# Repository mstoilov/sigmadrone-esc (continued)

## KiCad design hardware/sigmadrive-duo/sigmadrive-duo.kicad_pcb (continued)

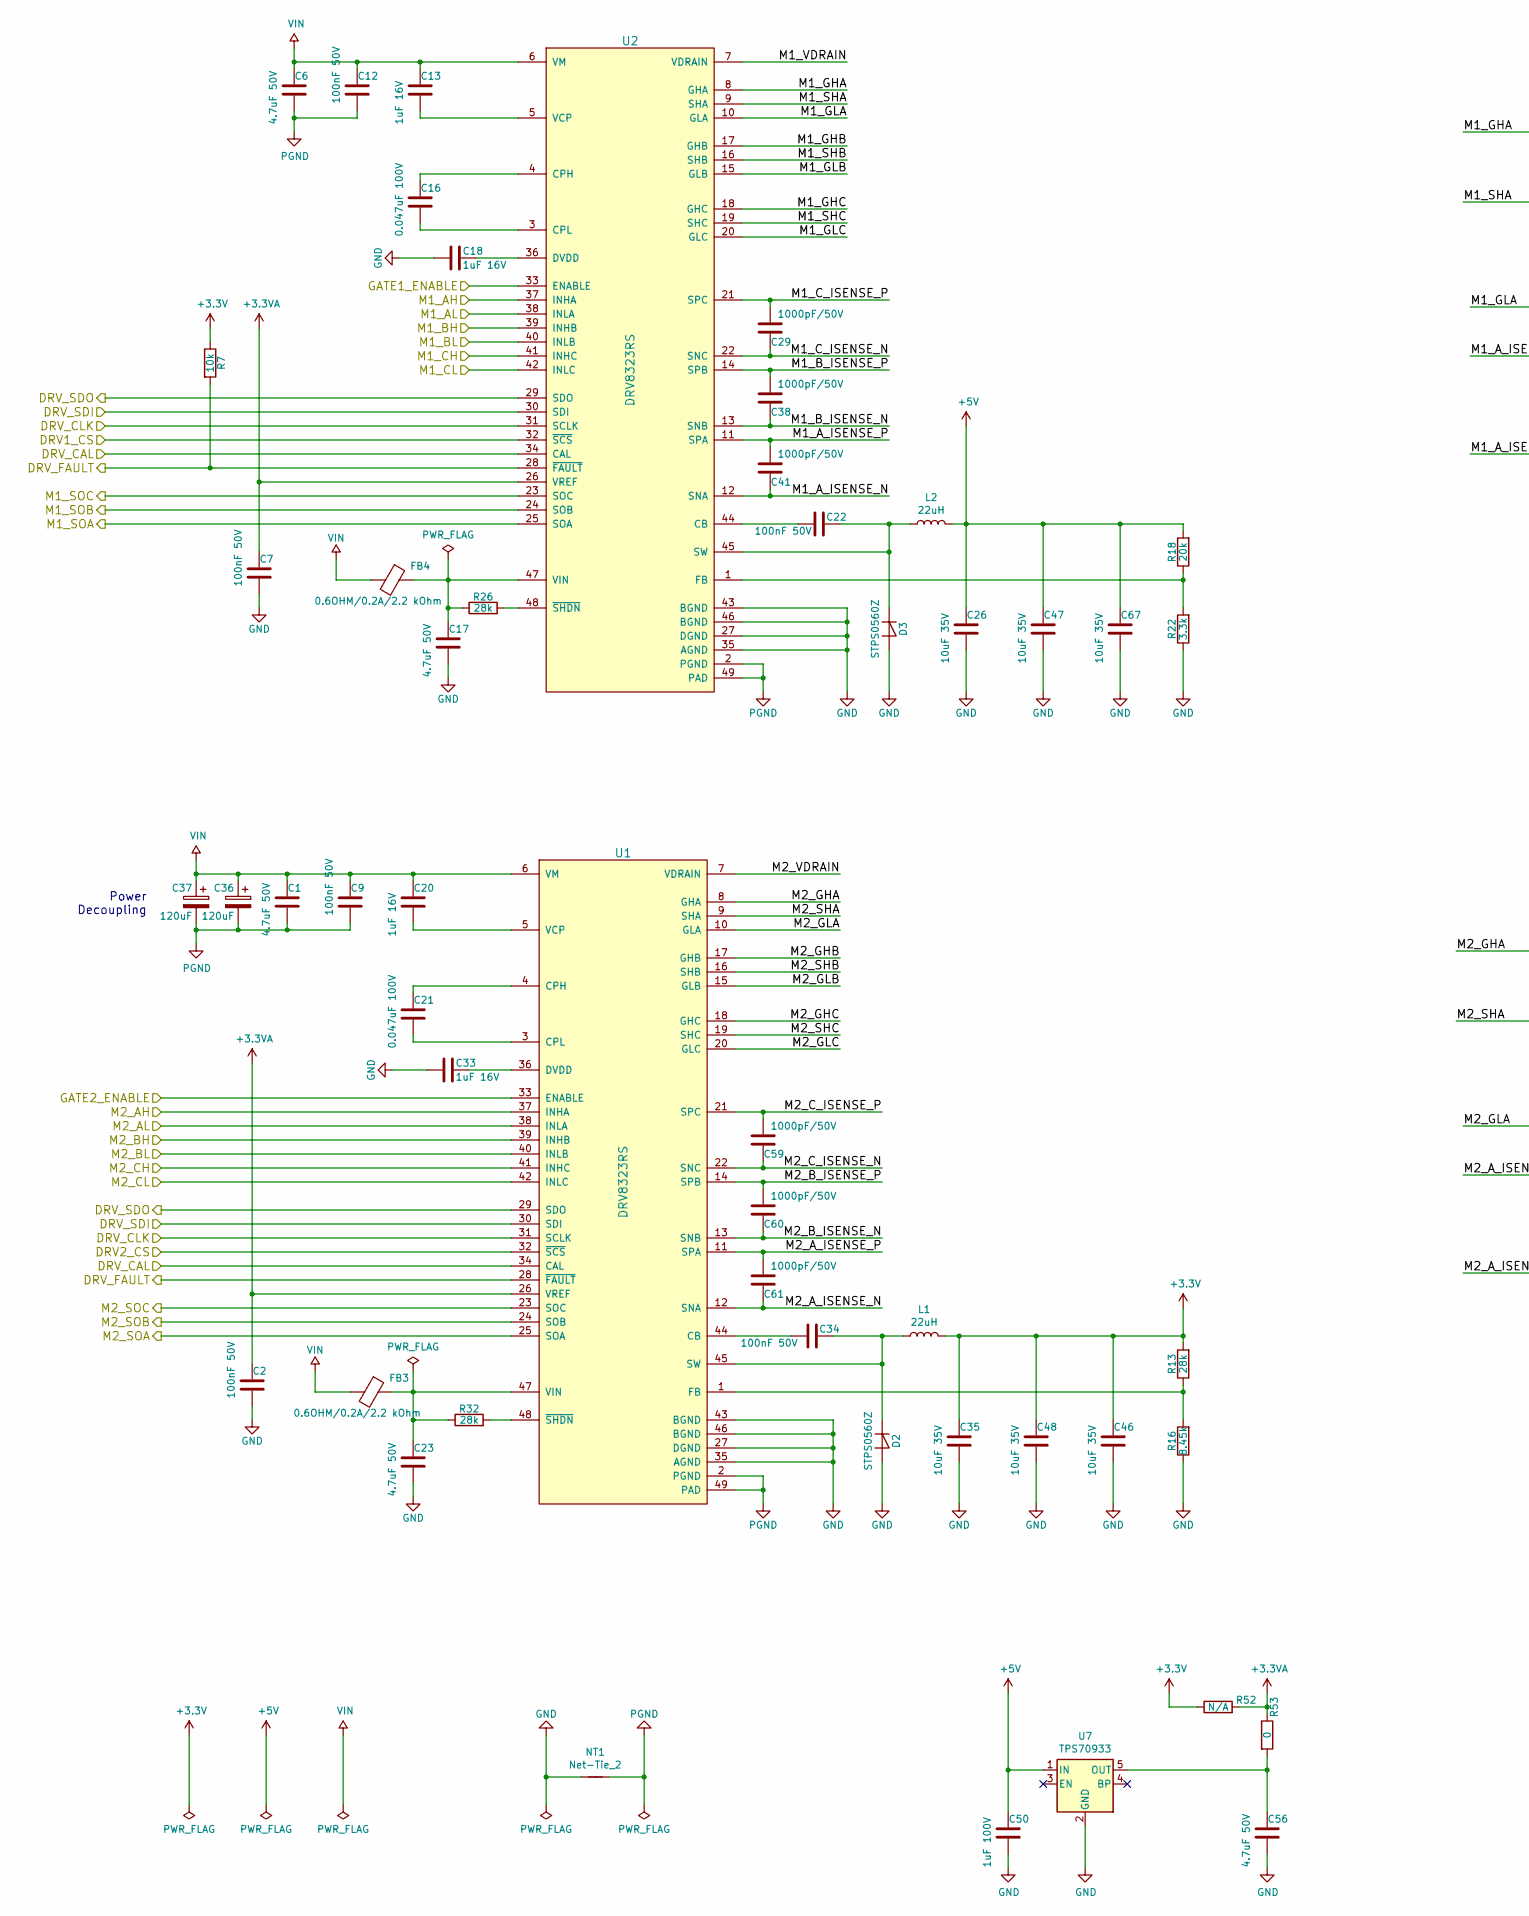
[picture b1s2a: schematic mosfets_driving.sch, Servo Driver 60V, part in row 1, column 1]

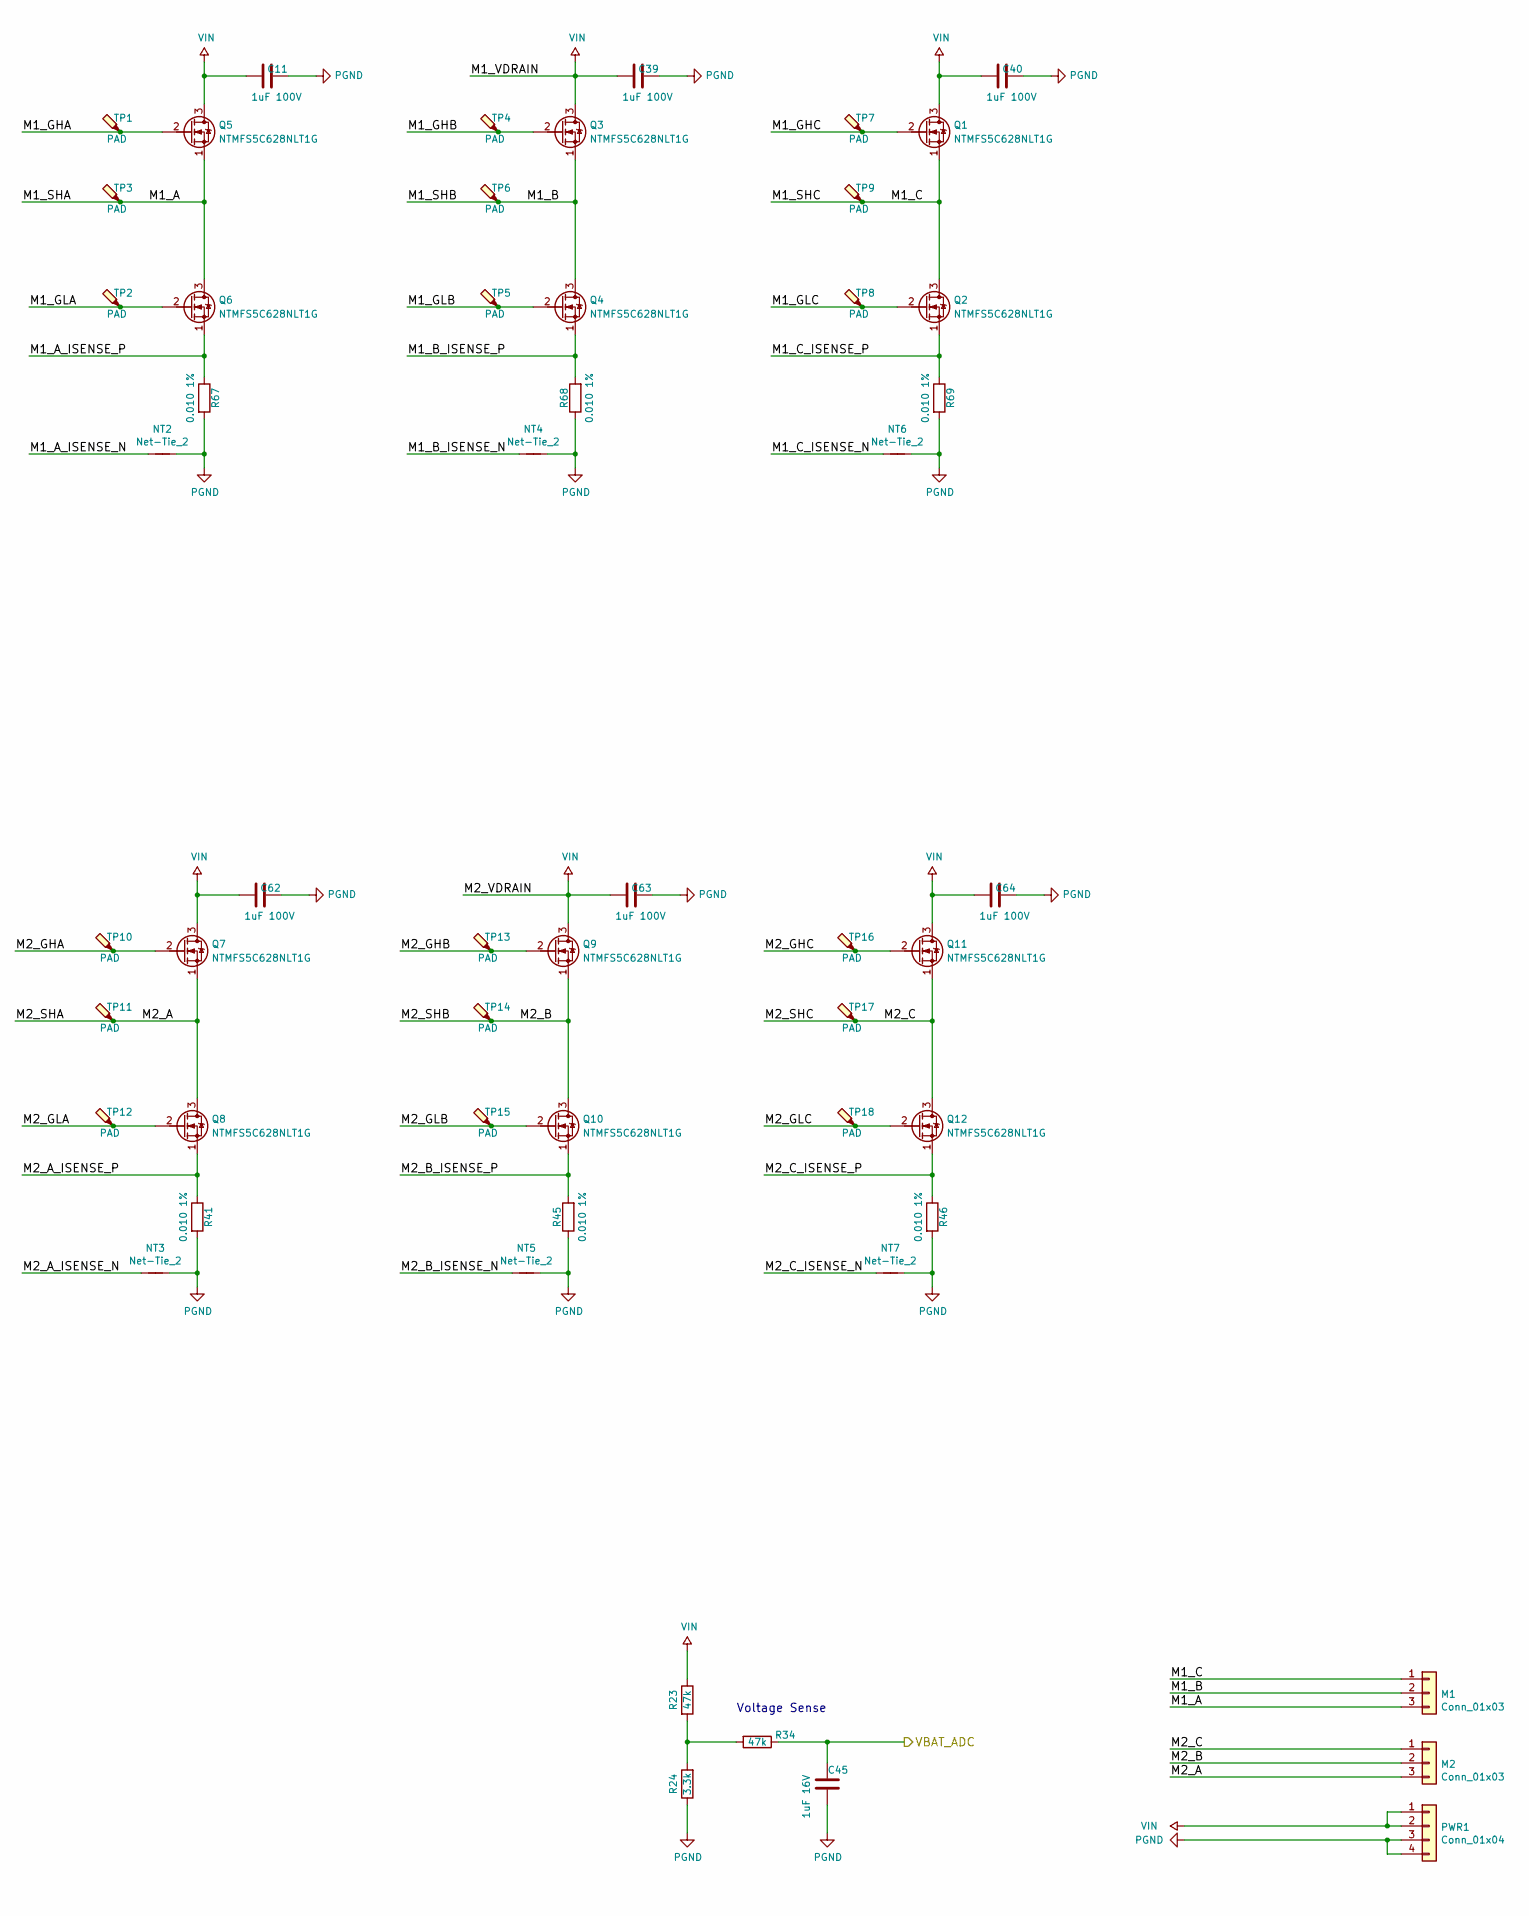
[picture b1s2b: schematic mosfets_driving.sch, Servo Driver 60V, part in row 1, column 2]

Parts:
C1, C6, C17, C23, C56: 4.7uF 50V; C_0805_2012Metric; Part 490-10751-2-ND
C2, C7, C9, C12, C22, C34: 100nF 50V; C_0603_1608Metric; Part 490-4779-2-ND
C11, C39, C40, C50, C62, C63, C64: 1uF 100V; C_0805_2012Metric; Part 445-6804-2-ND
C13, C18, C20, C33, C45: 1uF 16V; C_0603_1608Metric; Part 732-7971-1-ND
C16, C21: 0.047uF 100V; C_0805_2012Metric; Part 490-4969-1-ND
C26, C35, C46, C47, C48, C67: 10uF 35V; C_0805_2012Metric; Part 445-14419-6-ND
C29, C38, C41, C59, C60, C61: 1000pF/50V; C_0603_1608Metric; Part 1276-1091-2-ND
C36, C37: 120uF; CP_Elec_10x10; Part P19316CT-ND
D2, D3: STPS0560Z; D_SOD-123; Part 497-3787-1-ND
FB3, FB4: 0.6OHM/0.2A/2.2 kOhm; R_0603_1608Metric; Part 732-1609-1-ND
L1, L2: 22uH; L_Wuerth_WE-TPC-4828; Part 732-1107-1-ND
M1, M2: Conn_01x03; Molex_Micro-Fit_3.0_43650-0300_1x03_P3.00mm_Horizontal
NT1, NT2, NT3, NT4, NT5, NT6, NT7: Net-Tie_2; NetTie-2_SMD_Pad0.5mm
PWR1: Conn_01x04; Molex_Micro-Fit_3.0_43650-0400_1x04_P3.00mm_Horizontal
Q1, Q2, Q3, Q4, Q5, Q6, Q7, Q8, Q9, Q10, Q11, Q12: NTMFS5C628NLT1G; PQFN_5x6_SGD; Part NTMFS5C628NLT1GOSDKR-ND
R7: 10k; R_0603_1608Metric; Part 311-10.0KHRCT-ND
R13, R26, R32: 28k; R_0603_1608Metric; Part 311-28.0KHRCT-ND
R16: 8.45k; R_0603_1608Metric; Part 311-8.45KHRCT-ND
R18: 20k; R_0603_1608Metric; Part 311-20.0KHRTR-ND
R22, R24: 3.3k; R_0603_1608Metric; Part 311-3.30KHRCT-ND
R23, R34: 47k; R_0603_1608Metric; Part 311-47KDCT-ND
R41, R45, R46, R67, R68, R69: 0.010 1%; R_2512_6332Metric; Part CRA2512-FZ-R010ELFCT-ND
R52: N/A; R_0603_1608Metric; Part 311-0.0GRTR-ND
R53: 0; R_0603_1608Metric; Part 311-0.0GRTR-ND
TP1, TP2, TP3, TP4, TP5, TP6, TP7, TP8, TP9, TP10, TP11, TP12, TP13, TP14, TP15, TP16, TP17, TP18: PAD; TestPoint_Pad_D1.0mm
U1, U2: DRV8323RS; QFN-48-1EP_7x7mm_P0.5mm_EP5.45x5.45mm_ThermalVias; Part 296-47769-1-ND
U7: TPS70933; SOT-23-5; Part 296-35483-1-ND

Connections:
+3.3VA: C2.1, C7.1, R52.2, R53.1, U1.26 (VREF), U2.26 (VREF); also elsewhere on the board
+5V: C26.1, C47.1, C50.1, C67.1, L2.2, R18.2, U7.1 (IN); also elsewhere on the board
/MCU/DRV1_CS: U2.32 (~SCS); also elsewhere on the board
/MCU/DRV2_CS: U1.32 (~SCS); also elsewhere on the board
/MCU/DRV_CAL: U1.34 (CAL), U2.34 (CAL); also elsewhere on the board
/MCU/DRV_CLK: U1.31 (SCLK), U2.31 (SCLK); also elsewhere on the board
/MCU/DRV_FAULT: R7.2, U1.28 (~FAULT), U2.28 (~FAULT); also elsewhere on the board
/MCU/DRV_SDI: U1.30 (SDI), U2.30 (SDI); also elsewhere on the board
/MCU/DRV_SDO: U1.29 (SDO), U2.29 (SDO); also elsewhere on the board
/MCU/GATE1_ENABLE: U2.33 (ENABLE); also elsewhere on the board
/MCU/GATE2_ENABLE: U1.33 (ENABLE); also elsewhere on the board
/MCU/M1_AH: U2.37 (INHA); also elsewhere on the board
/MCU/M1_AL: U2.38 (INLA); also elsewhere on the board
/MCU/M1_BH: U2.39 (INHB); also elsewhere on the board
/MCU/M1_BL: U2.40 (INLB); also elsewhere on the board
/MCU/M1_CH: U2.41 (INHC); also elsewhere on the board
/MCU/M1_CL: U2.42 (INLC); also elsewhere on the board
/MCU/M1_IA_FB: U2.25 (SOA); also elsewhere on the board
/MCU/M1_IB_FB: U2.24 (SOB); also elsewhere on the board
/MCU/M1_IC_FB: U2.23 (SOC); also elsewhere on the board
/MCU/M2_AH: U1.37 (INHA); also elsewhere on the board
/MCU/M2_AL: U1.38 (INLA); also elsewhere on the board
/MCU/M2_BH: U1.39 (INHB); also elsewhere on the board
/MCU/M2_BL: U1.40 (INLB); also elsewhere on the board
/MCU/M2_CH: U1.41 (INHC); also elsewhere on the board
/MCU/M2_CL: U1.42 (INLC); also elsewhere on the board
/MCU/M2_IA_FB: U1.25 (SOA); also elsewhere on the board
/MCU/M2_IB_FB: U1.24 (SOB); also elsewhere on the board
/MCU/M2_IC_FB: U1.23 (SOC); also elsewhere on the board
/MCU/VBAT_ADC: C45.1, R34.1; also elsewhere on the board
/MOSFETs/M1_A: M1.3, Q5.1 (S), Q6.3 (D), TP3.1, U2.9 (SHA)
/MOSFETs/M1_A_ISENSE_N: C41.1, NT2.1, U2.12 (SNA)
/MOSFETs/M1_A_ISENSE_P: C41.2, Q6.1 (S), R67.1, U2.11 (SPA)
/MOSFETs/M1_B: M1.2, Q3.1 (S), Q4.3 (D), TP6.1, U2.16 (SHB)
/MOSFETs/M1_B_ISENSE_N: C38.1, NT4.1, U2.13 (SNB)
/MOSFETs/M1_B_ISENSE_P: C38.2, Q4.1 (S), R68.2, U2.14 (SPB)
/MOSFETs/M1_C: M1.1, Q1.1 (S), Q2.3 (D), TP9.1, U2.19 (SHC)
/MOSFETs/M1_C_ISENSE_N: C29.1, NT6.1, U2.22 (SNC)
/MOSFETs/M1_C_ISENSE_P: C29.2, Q2.1 (S), R69.1, U2.21 (SPC)
/MOSFETs/M1_GHA: Q5.2 (G), TP1.1, U2.8 (GHA)
/MOSFETs/M1_GHB: Q3.2 (G), TP4.1, U2.17 (GHB)
/MOSFETs/M1_GHC: Q1.2 (G), TP7.1, U2.18 (GHC)
/MOSFETs/M1_GLA: Q6.2 (G), TP2.1, U2.10 (GLA)
/MOSFETs/M1_GLB: Q4.2 (G), TP5.1, U2.15 (GLB)
/MOSFETs/M1_GLC: Q2.2 (G), TP8.1, U2.20 (GLC)
/MOSFETs/M2_A: M2.3, Q7.1 (S), Q8.3 (D), TP11.1, U1.9 (SHA)
/MOSFETs/M2_A_ISENSE_N: C61.1, NT3.1, U1.12 (SNA)
/MOSFETs/M2_A_ISENSE_P: C61.2, Q8.1 (S), R41.1, U1.11 (SPA)
/MOSFETs/M2_B: M2.2, Q9.1 (S), Q10.3 (D), TP14.1, U1.16 (SHB)
/MOSFETs/M2_B_ISENSE_N: C60.1, NT5.1, U1.13 (SNB)
/MOSFETs/M2_B_ISENSE_P: C60.2, Q10.1 (S), R45.2, U1.14 (SPB)
/MOSFETs/M2_C: M2.1, Q11.1 (S), Q12.3 (D), TP17.1, U1.19 (SHC)
/MOSFETs/M2_C_ISENSE_N: C59.1, NT7.1, U1.22 (SNC)
/MOSFETs/M2_C_ISENSE_P: C59.2, Q12.1 (S), R46.1, U1.21 (SPC)
/MOSFETs/M2_GHA: Q7.2 (G), TP10.1, U1.8 (GHA)
/MOSFETs/M2_GHB: Q9.2 (G), TP13.1, U1.17 (GHB)
/MOSFETs/M2_GHC: Q11.2 (G), TP16.1, U1.18 (GHC)
/MOSFETs/M2_GLA: Q8.2 (G), TP12.1, U1.10 (GLA)
/MOSFETs/M2_GLB: Q10.2 (G), TP15.1, U1.15 (GLB)
/MOSFETs/M2_GLC: Q12.2 (G), TP18.1, U1.20 (GLC)
GND: C2.2, C7.2, C17.2, C18.2, C23.2, C26.2, C33.2, C35.2, C46.2, C47.2, C48.2, C50.2, C56.2, C67.2, D2.2 (A), D3.2 (A), NT1.1, R16.1, R22.1, U1.27 (DGND), U1.35 (AGND), U1.43 (BGND), U1.46 (BGND), U2.27 (DGND), U2.35 (AGND), U2.43 (BGND), U2.46 (BGND), U7.2 (GND); also elsewhere on the board
unnamed: C13.2, U2.5 (VCP)
unnamed: C16.1, U2.4 (CPH)
unnamed: C16.2, U2.3 (CPL)
unnamed: C17.1, FB4.1, R26.1, U2.47 (VIN)
unnamed: C18.1, U2.36 (DVDD)
unnamed: C20.2, U1.5 (VCP)
unnamed: C21.1, U1.4 (CPH)
unnamed: C21.2, U1.3 (CPL)
unnamed: C22.1, U2.44 (CB)
unnamed: C22.2, D3.1 (K), L2.1, U2.45 (SW)
unnamed: C23.1, FB3.1, R32.1, U1.47 (VIN)
unnamed: C33.1, U1.36 (DVDD)
unnamed: C34.1, U1.44 (CB)
unnamed: C34.2, D2.1 (K), L1.1, U1.45 (SW)
unnamed: C56.1, R53.2, U7.5 (OUT)
unnamed: R13.1, R16.2, U1.1 (FB)
unnamed: R18.1, R22.2, U2.1 (FB)
unnamed: R23.2, R24.2, R34.2
unnamed: R26.2, U2.48 (~SHDN)
unnamed: R32.2, U1.48 (~SHDN)
PGND: C1.2, C6.2, C9.2, C11.2, C12.2, C36.2, C37.2, C39.2, C40.2, C45.2, C62.2, C63.2, C64.2, NT1.2, NT2.2, NT3.2, NT4.2, NT5.2, NT6.2, NT7.2, PWR1.3, PWR1.4, R24.1, R41.2, R45.1, R46.2, R67.2, R68.1, R69.2, U1.2 (PGND), U1.49 (PAD), U2.2 (PGND), U2.49 (PAD)
VIN: C1.1, C6.1, C9.1, C11.1, C12.1, C13.1, C20.1, C36.1, C37.1, C39.1, C40.1, C62.1, C63.1, C64.1, FB3.2, FB4.2, PWR1.1, PWR1.2, Q1.3 (D), Q3.3 (D), Q5.3 (D), Q7.3 (D), Q9.3 (D), Q11.3 (D), R23.1, U1.6 (VM), U1.7 (VDRAIN), U2.6 (VM), U2.7 (VDRAIN)

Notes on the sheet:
Power Decoupling
Voltage Sense

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
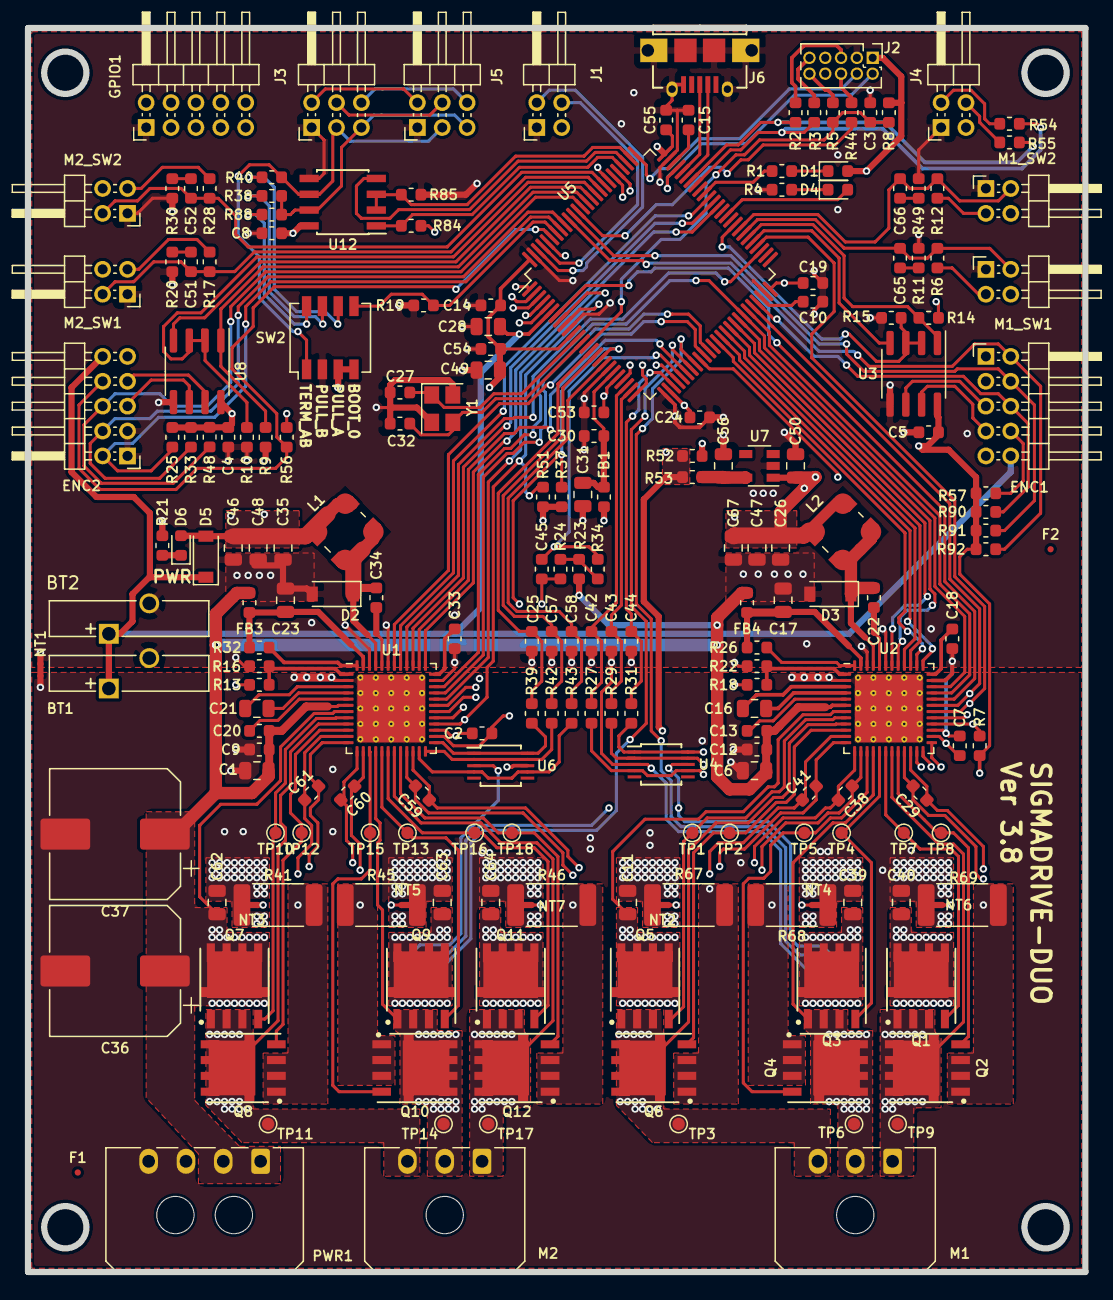
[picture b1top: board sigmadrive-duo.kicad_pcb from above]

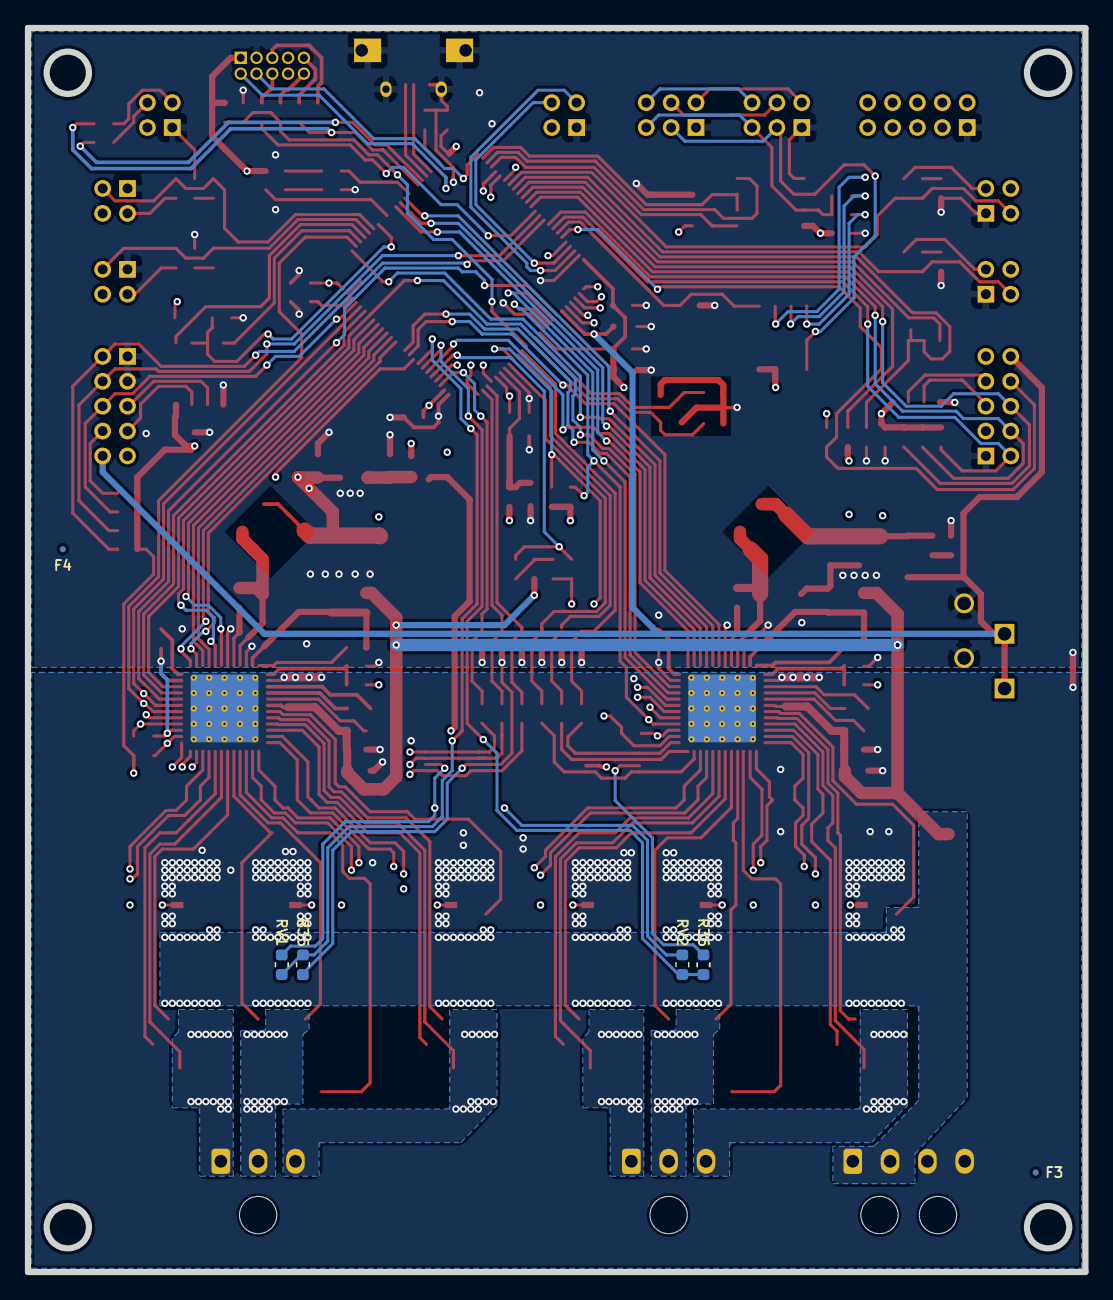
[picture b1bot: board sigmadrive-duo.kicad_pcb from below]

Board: 4 copper layers, 85.0 x 100.0 mm, 214 parts (6 on the bottom side), 166 nets.

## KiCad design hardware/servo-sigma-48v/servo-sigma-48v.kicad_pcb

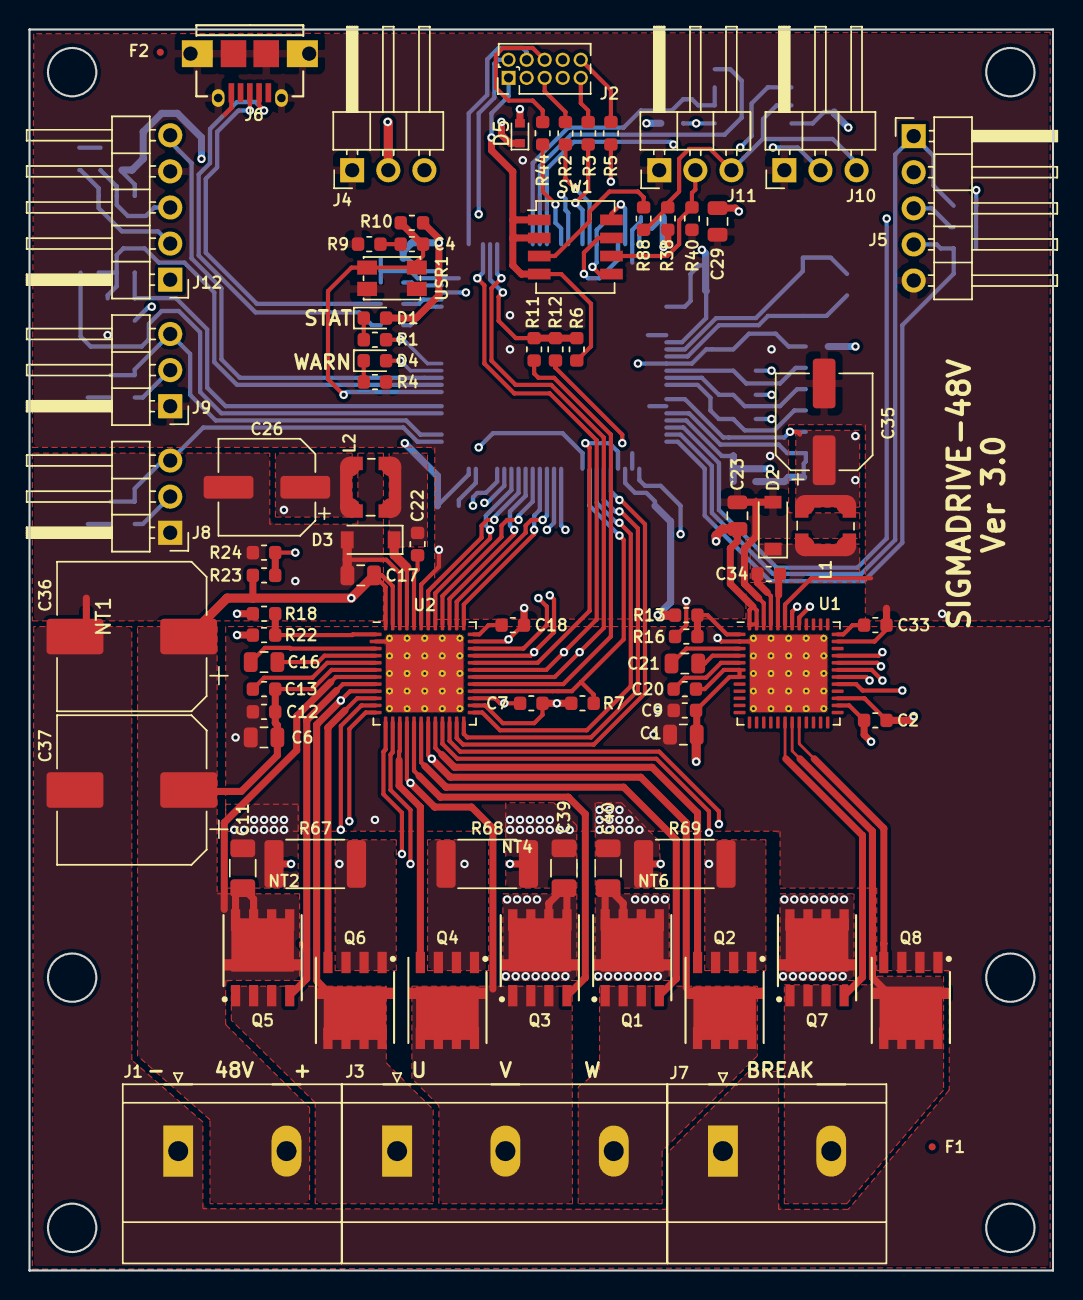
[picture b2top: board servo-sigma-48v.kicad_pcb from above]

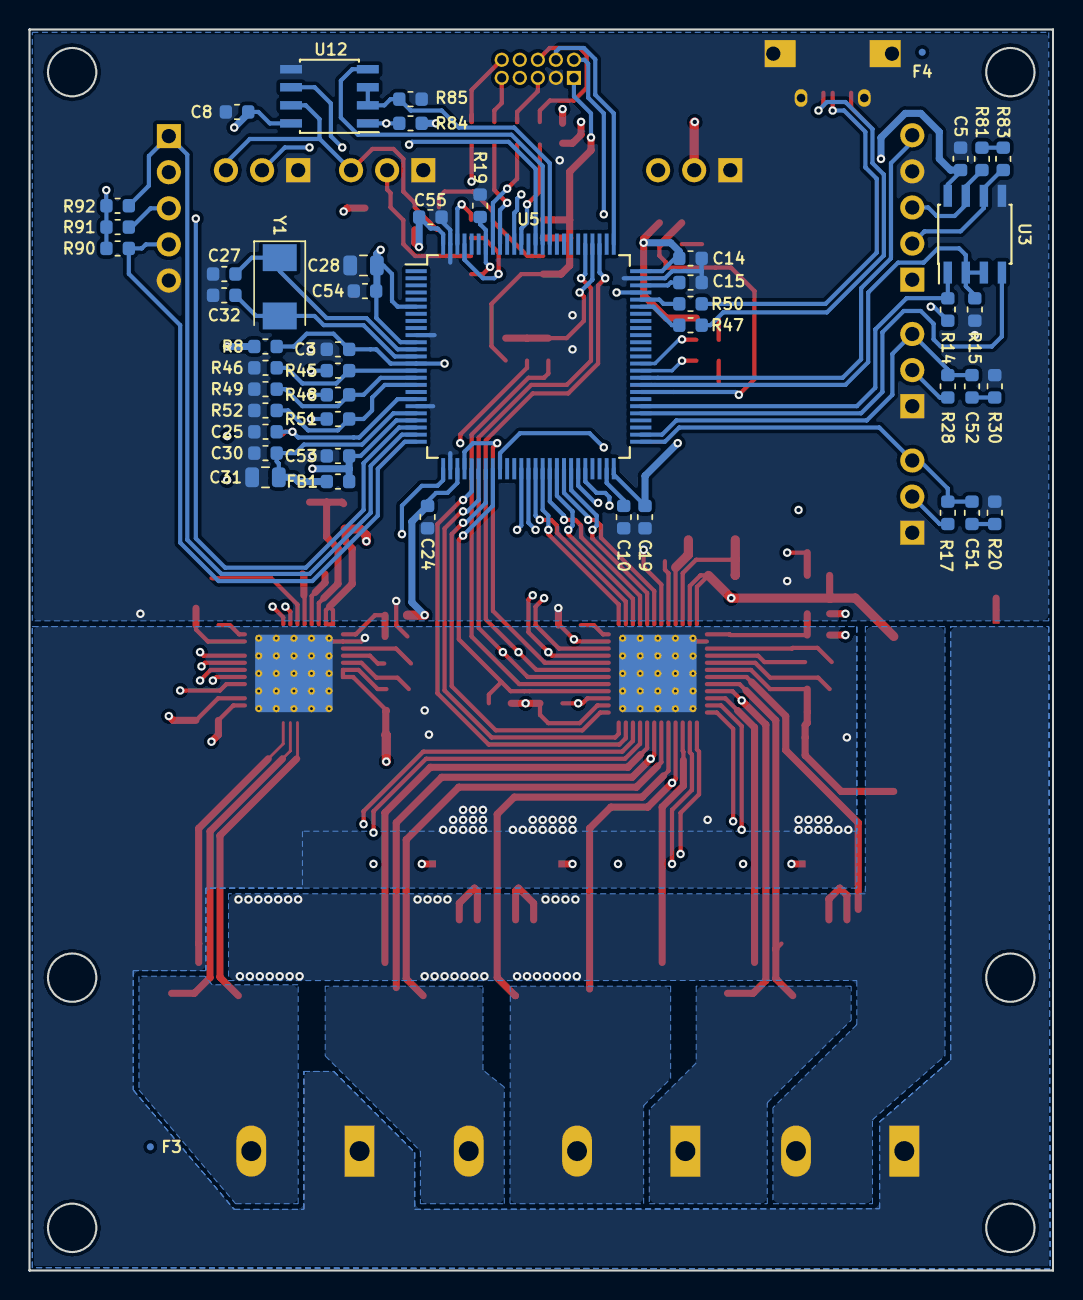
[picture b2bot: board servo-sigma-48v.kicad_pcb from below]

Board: 4 copper layers, 72.0 x 87.3 mm, 135 parts (49 on the bottom side), 112 nets.

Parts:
C1, C6, C17, C23: 4.7uF 50V; C_0805_2012Metric
C2, C7, C9, C12, C22, C34: 100nF; C_0603_1608Metric
C3, C4, C5, C8, C14, C19, C24, C25, C30, C51, C52, C53, C54, C55: 100nF 50V; C_0603_1608Metric
C10, C15: 2.2uF; C_0603_1608Metric
C11, C39, C40: 1uF 100V; C_1206_3216Metric
C13, C18, C20, C33: 1uF 16V; C_0603_1608Metric
C16, C21: 0.047uF 100V; C_0805_2012Metric
C26, C35: 100uF; CP_Elec_6.3x7.7
C27, C32: 27pF/50V/1%; C_0603_1608Metric
C28, C31: 1uF 100V; C_0805_2012Metric
C29: 4.7uF 25V; C_0805_2012Metric
C36, C37: 120uF; CP_Elec_10x10
D1: GREEN; LED_0603_1608Metric
D2, D3: STPS0560Z; D_SOD-123
D4: RED; LED_0603_1608Metric
D5: BAT30KFILM; D_SOD-523
F1, F2, F3, F4: FIDUCIAL; Fiducial_0.5mm_Dia_1mm_Outer
FB1: BEAD/0.6OHM/0.2A/2.2 kOhm @ 100MHz; R_0603_1608Metric
J1, J7: CONN_01X02; PhoenixContact_MKDS_02x7.62mm_Vertical
J2: CONN_02X05; PinHeader_2x05_P1.27mm_Vertical
J3: CONN_01X03; PhoenixContact_MKDS_03x7.62mm_Vertical
J4, J8, J9, J10, J11: Conn_01x03; PinHeader_1x03_P2.54mm_Horizontal
J5, J12: Conn_01x05; PinHeader_1x05_P2.54mm_Horizontal
J6: 629_105_150_921; WURTH_629105150921_NO_OVALS
L1, L2: 22uH; L_Wuerth_WE-TPC-3816
NT1, NT2, NT4, NT6: Net-Tie_2; NetTie-2_SMD_Pad0.5mm
Q1, Q2, Q3, Q4, Q5, Q6, Q7, Q8: STL160NS3LLH7; PQFN_5x6_SGD
R1, R4: 2.2k; R_0603_1608Metric
R2, R3, R5, R11, R12, R44, R47, R50, R83: 21; R_0603_1608Metric
R6, R7, R8, R10, R14, R15, R17, R19, R28, R84, R85, R90, R91, R92: 10k; R_0603_1608Metric
R9, R20, R30, R81, R88: 100; R_0603_1608Metric
R13: 28k; R_0603_1608Metric
R16: 8.45k; R_0603_1608Metric
R18: 18k; R_0603_1608Metric
R22: 3.3k; R_0603_1608Metric
R23, R45, R48, R51: 47k; R_0603_1608Metric
R24, R46, R49, R52: 4.7k; R_0603_1608Metric
R38, R40: N/A; R_0603_1608Metric
R67, R68, R69: 0.010 1%; R_2512_6332Metric
SW1: SW_DIP_x04; SW_DIP_SPSTx04_Slide_Copal_CHS-04A_W5.08mm_P1.27mm_JPin
U1, U2: DRV8323RS; QFN-48-1EP_7x7mm_P0.5mm_EP5.45x5.45mm_ThermalVias
U3, U12: SN65HVD75DGKR; SOIC-8_3.9x4.9mm_P1.27mm
U5: STM32F405VGTx; LQFP-100_14x14mm_P0.5mm
USR1: WURTH_434153017835; SW_SPST_WURTH_434153017835
Y1: ABM3-8.000MHZ-D2Y-T; Crystal_SMD_Abracon_ABM3-2Pin_5.0x3.2mm

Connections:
+3V3: C2.1, C5.2, C7.1, C8.2, C14.2, C19.2, C24.2, C25.2, C28.1, C29.2, C35.1, C53.2, C54.2, C55.2, D1.2, FB1.1, J2.1, L1.2, R6.1, R7.1, R8.2, R10.1, R13.2, R14.1, R38.2, R84.1, R90.1, R91.1, R92.1, SW1.1, SW1.2, SW1.4, U1.26, U2.26, U3.8, U5.6, U5.11, U5.19, U5.22, U5.28, U5.50, U5.75, U5.100, U12.8
+5V: C23.1, C26.1, D5.1, J4.2, J5.2, J8.2, J9.2, J12.1, L2.2, R17.1, R18.2, R28.1, U1.47, U1.48
/MCU/AUX_H: U1.41, U5.37
/MCU/AUX_L: U1.42, U5.38
/MCU/A_TERM_R120: J10.2, J11.2, R40.2, SW1.6, U12.6
/MCU/BOOT0: R19.1, SW1.5, U5.94
/MCU/B_TERM_R120: R88.2, SW1.3
/MCU/DRV1_CS: U2.32, U5.29
/MCU/DRV2_CS: U1.32, U5.26
/MCU/DRV_CAL: U2.34, U5.46
/MCU/DRV_CLK: U1.31, U2.31, U5.78
/MCU/DRV_FAULT: R7.2, U2.28, U5.33
/MCU/DRV_SDI: U1.30, U2.30, U5.80
/MCU/DRV_SDO: R6.2, R11.1, R12.1, U5.79
/MCU/ENCODER_A: J5.3, R91.2, U5.23
/MCU/ENCODER_B: J5.1, R92.2, U5.24
/MCU/ENCODER_DE: R15.1, U3.2, U3.3, U5.59
/MCU/ENCODER_DI: U3.4, U5.55
/MCU/ENCODER_RO: R14.2, U3.1, U5.56
/MCU/ENCODER_RS485_MCLR: J12.5, U5.60
/MCU/ENCODER_Z: J5.4, R90.2, U5.25
/MCU/EXT_5V: D5.2, J2.7
/MCU/GATE_ENABLE: U1.33, U2.33, U5.45
/MCU/GPIO_CONF_1: SW1.8, U5.98
/MCU/GPIO_CONF_2: SW1.7, U5.97
/MCU/LED_STATUS: R1.1, U5.62
/MCU/LED_WARN: D4.2, U5.61
/MCU/NRST: J2.10, R5.2
/MCU/PA11: R47.2, U5.70
/MCU/PA12: R50.2, U5.71
/MCU/PA13: J2.2, U5.72
/MCU/PA14: J2.4, U5.76
/MCU/PB3: R44.2, U5.89
/MCU/PB4: J4.3, U5.90
/MCU/PB6: R3.1, U5.92
/MCU/PB7: R2.1, U5.93
/MCU/PB12: C51.2, J8.3, R17.2, U5.51
/MCU/PB13: C52.2, J9.3, R28.2, U5.52
/MCU/PD4: R85.1, U5.85, U12.2, U12.3
/MCU/PD5: U5.86, U12.4
/MCU/PD6: R84.2, U5.87, U12.1
/MCU/PD11: C4.2, R10.2, U5.58, USR1.2
/MCU/PWM_AH: U2.37, U5.40
/MCU/PWM_AL: U2.38, U5.39
/MCU/PWM_BH: U2.39, U5.42
/MCU/PWM_BL: U2.40, U5.41
/MCU/PWM_CH: U2.41, U5.44
/MCU/PWM_CL: U2.42, U5.43
/MCU/SENSE_A: R51.1, R52.2, U5.17
/MCU/SENSE_B: R48.1, R49.2, U5.16
/MCU/SENSE_C: R45.1, R46.2, U5.15
/MCU/VBAT_ADC: R23.2, R24.1, U5.34
/MOSFETs/A_ISENSE_N: NT2.1, U2.12
/MOSFETs/A_ISENSE_P: Q6.1, R67.1, U2.11
/MOSFETs/B_ISENSE_N: NT4.1, U2.13
/MOSFETs/B_ISENSE_P: Q4.1, R68.1, U2.14
/MOSFETs/C_ISENSE_N: NT6.1, U2.22
/MOSFETs/C_ISENSE_P: Q2.1, R69.1, U2.21
/MOSFETs/DRV_SOA: U2.25, U5.32
/MOSFETs/DRV_SOB: U2.24, U5.31
/MOSFETs/DRV_SOC: U2.23, U5.30
/MOSFETs/GHA: Q5.2, U2.8
/MOSFETs/GHB: Q3.2, U2.17
/MOSFETs/GHC: Q1.2, U2.18
/MOSFETs/GHR: Q7.2, U1.18
/MOSFETs/GLA: Q6.2, U2.10
/MOSFETs/GLB: Q4.2, U2.15
/MOSFETs/GLC: Q2.2, U2.20
/MOSFETs/GLR: Q8.2, U1.20
/MOSFETs/PHASE_A: J3.1, Q5.1, Q6.3, R51.2, U2.9
/MOSFETs/PHASE_B: J3.2, Q3.1, Q4.3, R48.2, U2.16
/MOSFETs/PHASE_C: J3.3, Q1.1, Q2.3, R45.2, U2.19
/MOSFETs/PHASE_R: J7.2, Q7.1, Q8.3, U1.19
GND: C2.2, C3.1, C5.1, C7.2, C8.1, C10.1, C14.1, C15.1, C17.2, C18.2, C19.1, C23.2, C24.1, C25.1, C26.2, C27.2, C28.2, C29.1, C30.2, C31.2, C32.2, C33.2, C35.2, C53.1, C54.1, C55.1, D2.2, D3.2, J2.3, J4.1, J5.5, J6.5, J6.6, J6.7, J6.8, J6.9, J6.10, J6.11, J8.1, J9.1, J10.1, J11.1, J12.4, NT1.1, R4.1, R9.1, R15.2, R16.1, R19.2, R20.2, R22.1, R24.2, R30.2, R40.1, R46.1, R49.1, R52.1, R85.2, U1.27, U1.35, U1.43, U1.46, U2.27, U2.35, U2.43, U2.46, U3.5, U5.10, U5.20, U5.27, U5.74, U5.99, U12.5, USR1.1
unnamed: C3.2, R5.1, R8.1, U5.14
unnamed: C4.1, R9.2
unnamed: C10.2, U5.49
unnamed: C13.2, U2.5
unnamed: C15.2, U5.73
unnamed: C16.1, U2.4
unnamed: C16.2, U2.3
unnamed: C18.1, U2.36
unnamed: C20.2, U1.5
unnamed: C21.1, U1.4
unnamed: C21.2, U1.3
unnamed: C22.1, U2.44
unnamed: C22.2, D3.1, L2.1, U2.45
unnamed: C27.1, U5.12, Y1.1
unnamed: C30.1, C31.1, FB1.2, U5.21
unnamed: C32.1, U5.13, Y1.2
unnamed: C33.1, U1.36
unnamed: C34.1, U1.44
unnamed: C34.2, D2.1, L1.1, U1.45
unnamed: C51.1, R20.1
unnamed: C52.1, R30.1
unnamed: D1.1, R1.2
unnamed: D4.1, R4.2
unnamed: J2.5, R2.2
unnamed: J2.6, R44.1
unnamed: J2.9, R3.2
unnamed: J6.2, R47.1
unnamed: J6.3, R50.1
unnamed: J10.3, J11.3, R38.1, R88.1, U12.7
unnamed: J12.2, R83.2, U3.6
unnamed: J12.3, R81.1, U3.7
unnamed: R11.2, U2.29
unnamed: R12.2, U1.29
unnamed: R13.1, R16.2, U1.1
unnamed: R18.1, R22.2, U2.1
unnamed: R81.2, R83.1
PGND: C1.2, C6.2, C9.2, C11.2, C12.2, C36.2, C37.2, C39.2, C40.2, J1.1, J7.1, NT1.2, NT2.2, NT4.2, NT6.2, Q8.1, R67.2, R68.2, R69.2, U1.2, U1.49, U2.2, U2.49
VIN: C1.1, C6.1, C9.1, C11.1, C12.1, C13.1, C17.1, C20.1, C36.1, C37.1, C39.1, C40.1, J1.2, Q1.3, Q3.3, Q5.3, Q7.3, R23.1, U1.6, U1.7, U2.6, U2.7, U2.47, U2.48

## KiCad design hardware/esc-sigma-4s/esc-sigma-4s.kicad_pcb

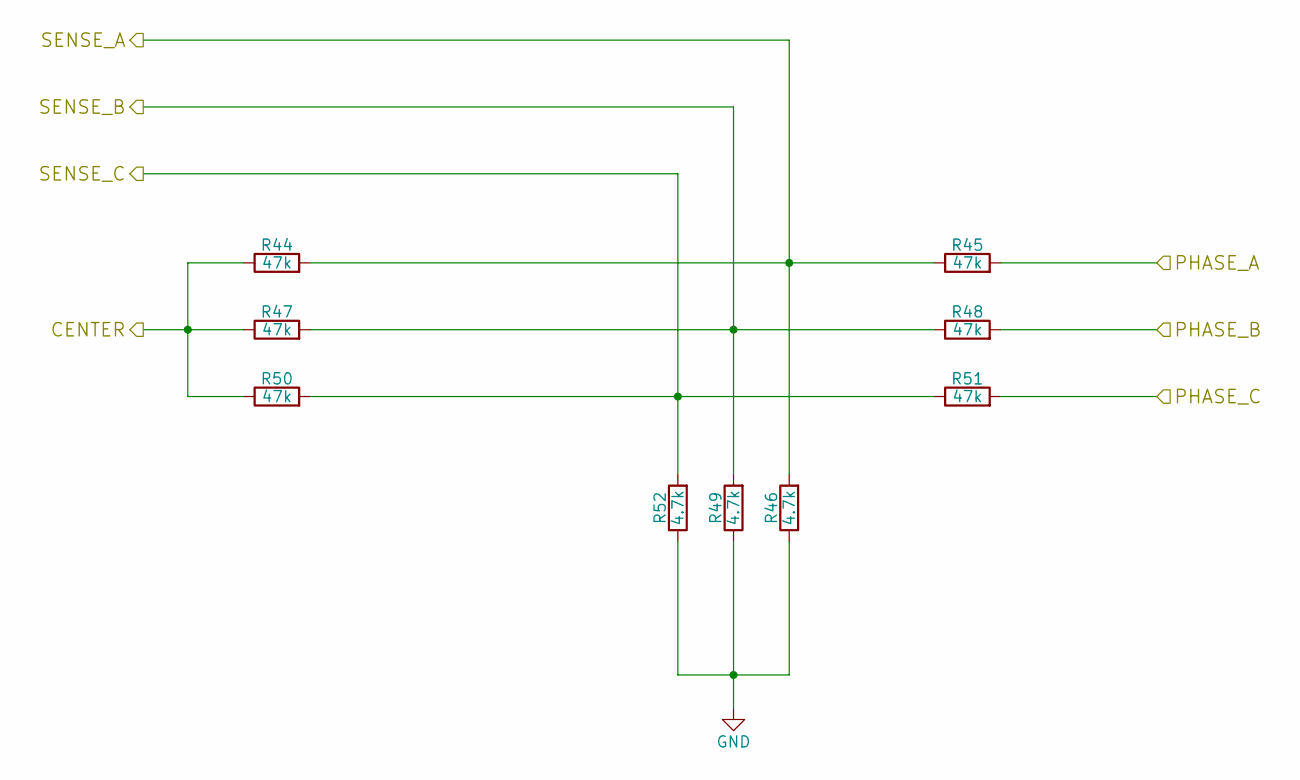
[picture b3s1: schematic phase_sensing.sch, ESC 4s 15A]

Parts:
R44, R45, R47, R48, R50, R51: 47k; R_0603; Part 311-47KDCT-ND
R46, R49, R52: 4.7k; R_0603; Part 311-2606-2-ND

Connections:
/MCU/CENTER: R44.1, R47.1, R50.1; also elsewhere on the board
/MCU/SENSE_A: R44.2, R45.1, R46.2; also elsewhere on the board
/MCU/SENSE_B: R47.2, R48.1, R49.2; also elsewhere on the board
/MCU/SENSE_C: R50.2, R51.1, R52.2; also elsewhere on the board
/MOSFETs/PHASE_A: R45.2; also elsewhere on the board
/MOSFETs/PHASE_B: R48.2; also elsewhere on the board
/MOSFETs/PHASE_C: R51.2; also elsewhere on the board
GND: R46.1, R49.1, R52.1; also elsewhere on the board
